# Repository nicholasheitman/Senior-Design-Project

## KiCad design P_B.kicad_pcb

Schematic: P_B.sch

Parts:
D1: D; D_MELF-RM10_Universal_Handsoldering
J1: Barrel_Jack
J2: Screw_Terminal_01x02; TerminalBlock_Pheonix_PT-3.5mm_2pol
R1: R; R_0805_HandSoldering
SHIELD1: ARDUINO_SHIELD; ARDUINO SHIELD
T1: TRANSISTOR-NPN-BIPOLAR_EN60617_Derived05-05-02_Da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; OldSowjetaera_Transistor_Type-II_SmallPads
U1: 16x2_LCD; Pin_Header_Straight_1x16_Pitch2.54mm
U2: HSC_Sensor; HSCDAND015PDSA3
U3: Potentiometer; Potentiometer_Bourns_3296W_3-8Zoll_Inline_ScrewUp
U5: RELAY; JZC-11F

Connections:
/3_3VDD: SHIELD1.3V3, U2.2 (VDD)
/5VDD: D1.1 (K), R1.2, SHIELD1.5V, U1.2 (5VDD), U1.15 (LED+), U3.1 (Vin), U5.1
/D2: SHIELD1.2
/D3: SHIELD1.3, U1.13 (DB6)
/D4: SHIELD1.4, U1.12 (DP5)
/D5: SHIELD1.5, U1.11 (DP4)
/D6: SHIELD1.6, U1.14 (DB7)
/D7: SHIELD1.7, U1.6 (EN)
/D8: SHIELD1.8, U1.4 (RS)
/MISO: SHIELD1.12, U2.3 (MISO)
/S1: J1.1, SHIELD1.V_IN, U5.3
/SCLK: SHIELD1.13, U2.4 (SCLK)
/SS: SHIELD1.10, U2.5 (SS)
/Vout: U1.3 (Contrast), U3.2 (Vout)
GND: J1.2, J1.3, J2.2, SHIELD1.GND1, T1.3 (E), U1.1 (GND), U1.16 (LED-), U2.1 (GND), U3.3 (GND)
unnamed: D1.2 (A), T1.1 (C), U5.2
unnamed: J2.1, U5.5
unnamed: R1.1, T1.2 (B)

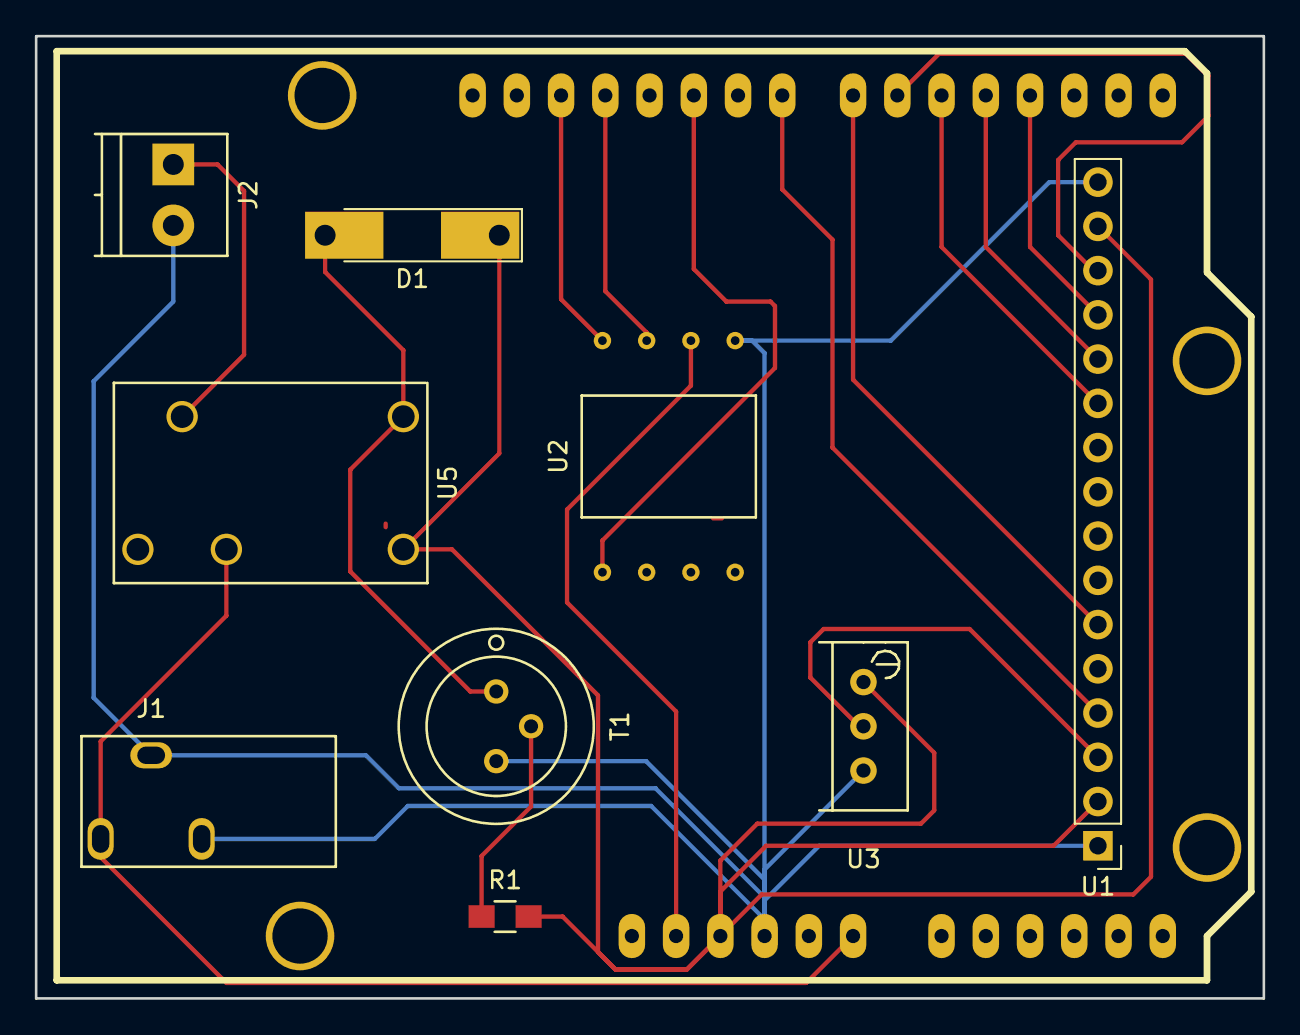
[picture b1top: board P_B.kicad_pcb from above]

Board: 2 copper layers, 70.5 x 55.2 mm, 10 parts (0 on the bottom side), 17 nets.
